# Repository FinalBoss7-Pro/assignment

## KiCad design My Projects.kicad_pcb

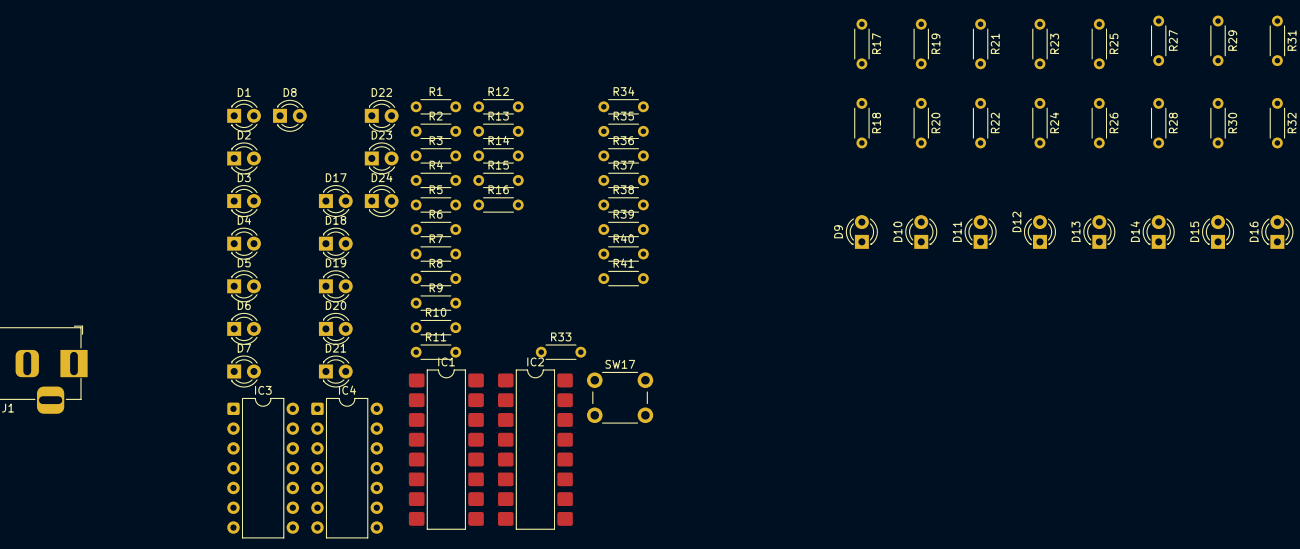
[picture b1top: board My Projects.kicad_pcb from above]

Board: 2 copper layers, 71 parts (0 on the bottom side), 60 nets, no tracks yet.

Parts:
D1, D2, D3, D4, D5, D6, D7, D8, D9, D10, D11, D12, D13, D14, D15, D16, D17, D18, D19, D20, D21, D22, D23, D24: LED; LED_D3.0mm
IC1, IC2: 7483; SMDIP-16_W7.62mm
IC3, IC4: 7486; DIP-14_W7.62mm
J1: Barrel_Jack; BarrelJack_Horizontal
R1, R2, R3, R4, R5, R6, R7, R8, R9, R10, R11, R12, R13, R14, R15, R16, R17, R18, R19, R20, R21, R22, R23, R24, R25, R26, R27, R28, R29, R30, R31, R32: 1K; R_Axial_DIN0204_L3.6mm_D1.6mm_P5.08mm_Horizontal
R33, R34, R35, R36, R37, R38, R39, R40: 1k; R_Axial_DIN0204_L3.6mm_D1.6mm_P5.08mm_Horizontal
R41: R; R_Axial_DIN0204_L3.6mm_D1.6mm_P5.08mm_Horizontal
SW17: SW_Push; SW_PUSH_6mm

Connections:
/A0: IC2.10 (A1), R1.2, R2.1
/A1: IC2.8 (A2), R3.2, R4.1
/A2: IC2.3 (A3), R5.2, R6.1
/A3: IC2.1 (A4), R7.2, R8.1
/A4: IC1.10 (A1), R9.2, R10.1
/A5: IC1.8 (A2), R11.2, R12.1
/A6: IC1.3 (A3), R13.2, R14.1
/A7: IC1.1 (A4), R15.2, R16.1
/B0: IC4.12, R17.2, R18.1
/B1: IC4.9, R19.2, R20.1
/B2: IC4.4, R21.2, R22.1
/B3: IC4.1, R23.2, R24.1
/B4: IC3.12, R25.2, R26.1
/B5: IC3.9, R27.2, R28.1
/B6: IC3.4, R29.2, R30.1
/B7: IC3.1, R31.2, R32.1
/S0: IC2.9 (S0), R33.1
/S1: IC2.6 (S1), R34.1
/S2: IC2.2 (S2), R35.1
/S3: IC2.15 (S3), R36.1
/S4: IC1.9 (S0), R37.1
/S5: IC1.6 (S1), R38.1
/S6: IC1.2 (S2), R39.1
/S7: IC1.15 (S3), R40.1
/SUB: IC2.13 (C0), IC3.2, IC3.5, IC3.10, IC3.13, IC4.2, IC4.5, IC4.10, IC4.13, R41.2, SW17.2
/VCC: IC1.5 (VCC), IC2.5 (VCC), IC3.14 (Vcc), IC4.14 (Vcc), J1.1, R1.1, R3.1, R5.1, R7.1, R9.1, R11.1, R13.1, R15.1, R17.1, R19.1, R21.1, R23.1, R25.1, R27.1, R29.1, R31.1, R41.1
GND: D1.1 (K), D2.1 (K), D3.1 (K), D4.1 (K), D5.1 (K), D6.1 (K), D7.1 (K), D8.1 (K), D9.1 (K), D10.1 (K), D11.1 (K), D12.1 (K), D13.1 (K), D14.1 (K), D15.1 (K), D16.1 (K), D17.1 (K), D18.1 (K), D19.1 (K), D20.1 (K), D21.1 (K), D22.1 (K), D23.1 (K), D24.1 (K), IC1.12 (GND), IC2.12 (GND), IC3.7 (GND), IC4.7 (GND), J1.2, SW17.1
unnamed: D1.2 (A), R2.2
unnamed: D2.2 (A), R4.2
unnamed: D3.2 (A), R6.2
unnamed: D4.2 (A), R8.2
unnamed: D5.2 (A), R10.2
unnamed: D6.2 (A), R12.2
unnamed: D7.2 (A), R14.2
unnamed: D8.2 (A), R16.2
unnamed: D9.2 (A), R18.2
unnamed: D10.2 (A), R20.2
unnamed: D11.2 (A), R22.2
unnamed: D12.2 (A), R24.2
unnamed: D13.2 (A), R26.2
unnamed: D14.2 (A), R28.2
unnamed: D15.2 (A), R30.2
unnamed: D16.2 (A), R32.2
unnamed: D17.2 (A), R33.2
unnamed: D18.2 (A), R34.2
unnamed: D19.2 (A), R35.2
unnamed: D20.2 (A), R36.2
unnamed: D21.2 (A), R37.2
unnamed: D22.2 (A), R38.2
unnamed: D23.2 (A), R39.2
unnamed: D24.2 (A), R40.2
unnamed: IC1.11 (B1), IC3.11
unnamed: IC1.7 (B2), IC3.8
unnamed: IC1.4 (B3), IC3.6
unnamed: IC1.16 (B4), IC3.3
unnamed: IC1.13 (C0), IC2.14 (C4)
unnamed: IC2.11 (B1), IC4.11
unnamed: IC2.7 (B2), IC4.8
unnamed: IC2.4 (B3), IC4.6
unnamed: IC2.16 (B4), IC4.3

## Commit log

2025-12-01 footprint added
